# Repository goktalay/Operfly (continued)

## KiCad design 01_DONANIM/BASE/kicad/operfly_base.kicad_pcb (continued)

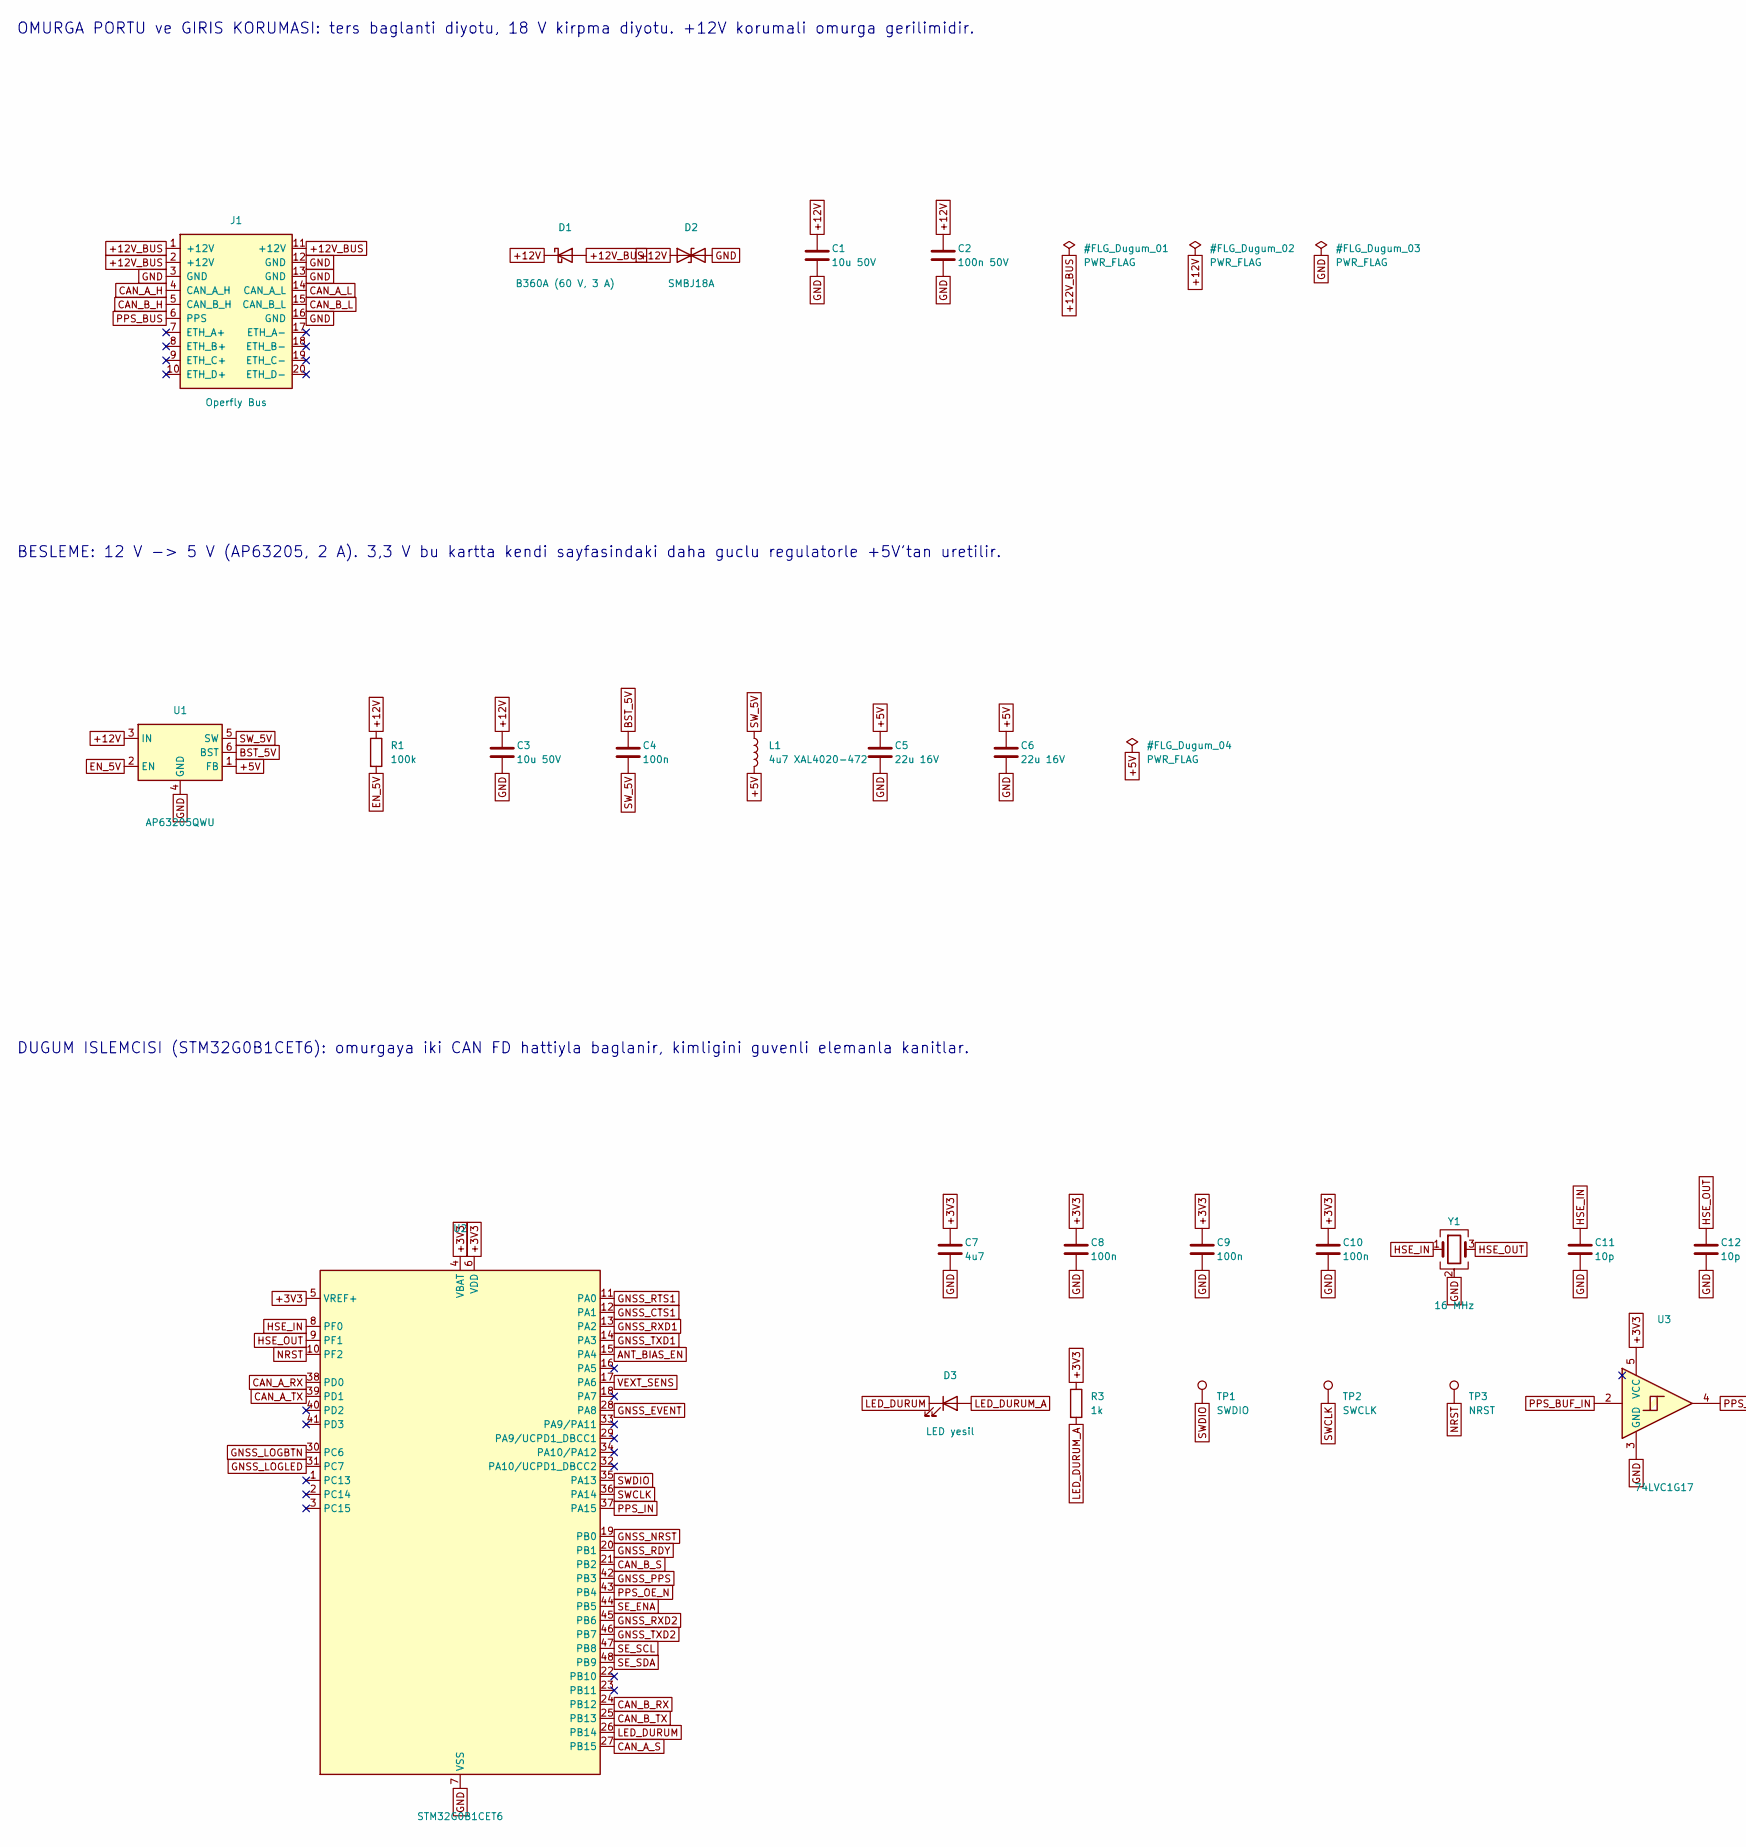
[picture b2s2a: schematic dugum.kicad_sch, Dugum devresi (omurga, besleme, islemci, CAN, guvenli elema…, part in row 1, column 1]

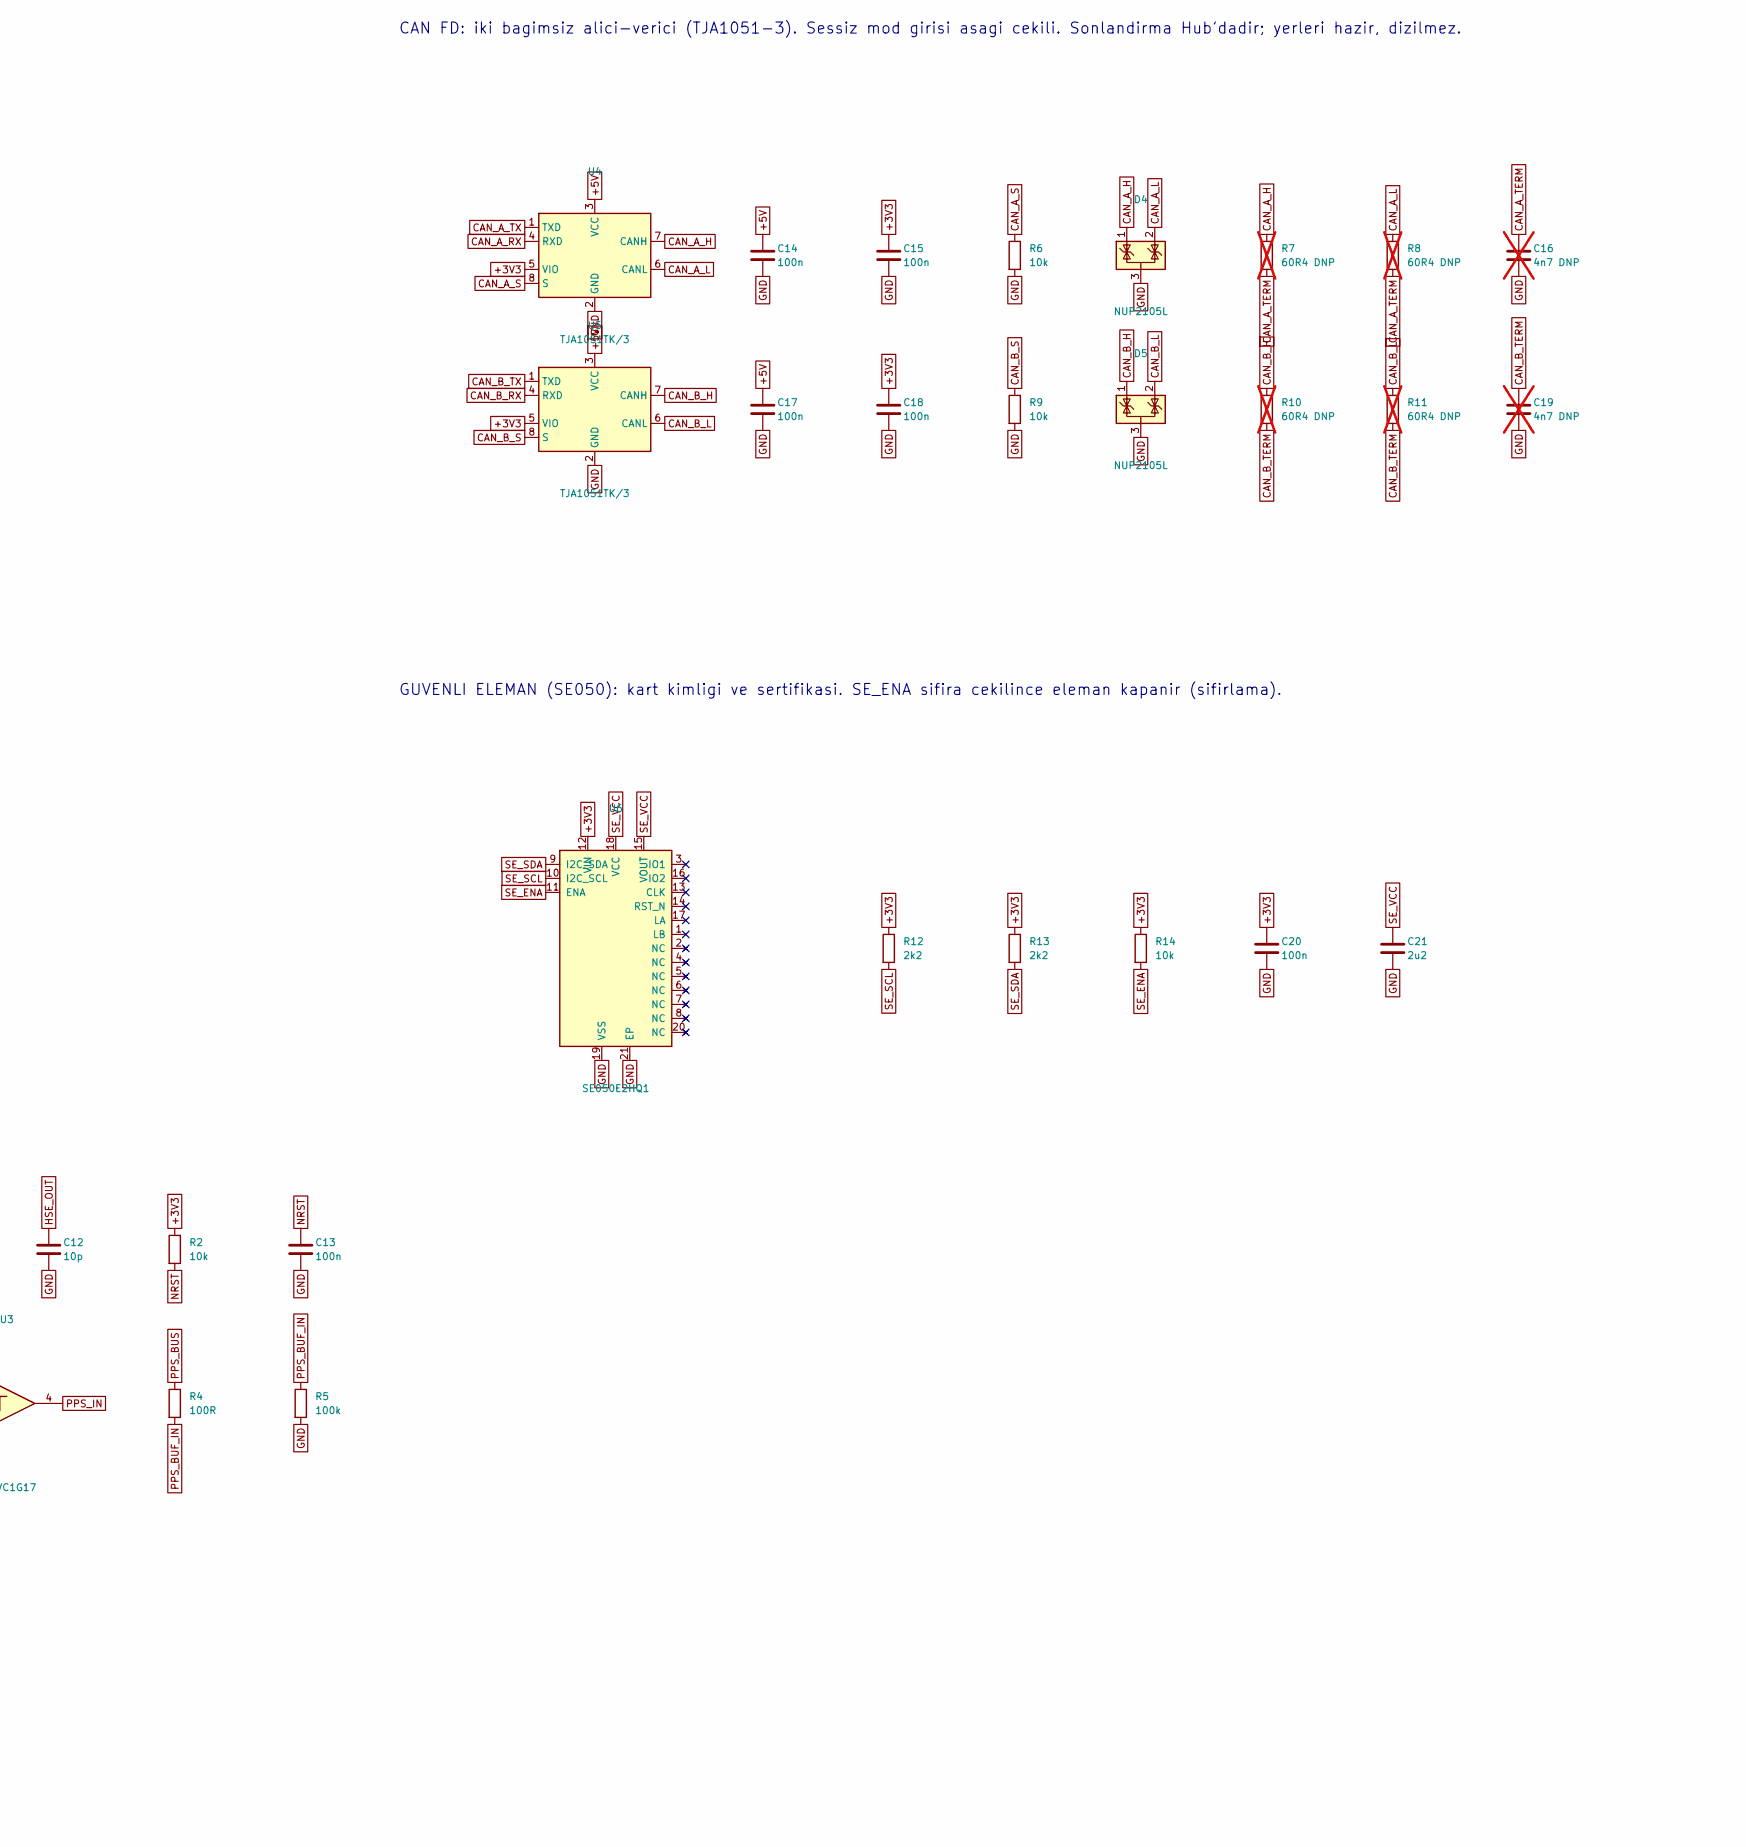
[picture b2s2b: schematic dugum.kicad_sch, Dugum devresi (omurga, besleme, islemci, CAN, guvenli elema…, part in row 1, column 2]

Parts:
C1, C3: 10u 50V; C_1206_3216Metric
C2: 100n 50V; C_0603_1608Metric
C4, C8, C9, C10, C13, C14, C15, C17, C18, C20: 100n; C_0402_1005Metric
C5, C6: 22u 16V; C_1206_3216Metric
C7: 4u7; C_0603_1608Metric
C11, C12: 10p; C_0402_1005Metric
C16, C19: 4n7 DNP; C_0402_1005Metric; not fitted
C21: 2u2; C_0603_1608Metric
D1: B360A (60 V, 3 A); D_SMA
D2: SMBJ18A; D_SMB
D3: LED yesil; LED_0603_1608Metric
D4, D5: NUP2105L; SOT-23
J1: Operfly Bus; Harwin_Gecko_G125-MS12005M2P_2x10_P1.25mm_Vertical
L1: 4u7 XAL4020-472; L_Coilcraft_XAL4020-XXX
R1, R5: 100k; R_0402_1005Metric
R2, R6, R9, R14: 10k; R_0402_1005Metric
R3: 1k; R_0402_1005Metric
R4: 100R; R_0402_1005Metric
R7, R8, R10, R11: 60R4 DNP; R_0402_1005Metric; not fitted
R12, R13: 2k2; R_0402_1005Metric
TP1: SWDIO; TestPoint_Pad_D1.0mm
TP2: SWCLK; TestPoint_Pad_D1.0mm
TP3: NRST; TestPoint_Pad_D1.0mm
U1: AP63205QWU; TSOT-23-6
U2: STM32G0B1CET6; LQFP-48_7x7mm_P0.5mm
U3: 74LVC1G17; SOT-353_SC-70-5
U4, U5: TJA1051TK/3; HVSON-8-1EP_3x3mm_P0.65mm_EP1.6x2.4mm
U6: SE050E2HQ1; QFN-20-1EP_3x3mm_P0.4mm_EP1.65x1.65mm
Y1: 16 MHz; Crystal_SMD_3225-4Pin_3.2x2.5mm

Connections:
+3V3: C7.1, C8.1, C9.1, C10.1, C15.1, C18.1, C20.1, R2.1, R3.1, R12.1, R13.1, R14.1, U2.4 (VBAT), U2.5 (VREF+), U2.6 (VDD), U3.5 (VCC), U4.5 (VIO), U5.5 (VIO), U6.12 (VIN); also elsewhere on the board
+5V: C5.1, C6.1, C14.1, C17.1, L1.2, U1.1 (FB), U4.3 (VCC), U5.3 (VCC); also elsewhere on the board
+12V: C1.1, C2.1, C3.1, D1.1 (K), D2.1 (A1), R1.1, U1.3 (IN); also elsewhere on the board
+12V_BUS: D1.2 (A), J1.1 (+12V), J1.2 (+12V), J1.11 (+12V)
ANT_BIAS_EN: U2.15 (PA4); also elsewhere on the board
BST_5V: C4.1, U1.6 (BST)
CAN_A_H: D4.1 (K), J1.4 (CAN_A_H), R7.1, U4.7 (CANH)
CAN_A_L: D4.2 (K), J1.14 (CAN_A_L), R8.1, U4.6 (CANL)
CAN_A_RX: U2.38 (PD0), U4.4 (RXD)
CAN_A_S: R6.1, U2.27 (PB15), U4.8 (S)
CAN_A_TERM: C16.1, R7.2, R8.2
CAN_A_TX: U2.39 (PD1), U4.1 (TXD)
CAN_B_H: D5.1 (K), J1.5 (CAN_B_H), R10.1, U5.7 (CANH)
CAN_B_L: D5.2 (K), J1.15 (CAN_B_L), R11.1, U5.6 (CANL)
CAN_B_RX: U2.24 (PB12), U5.4 (RXD)
CAN_B_S: R9.1, U2.21 (PB2), U5.8 (S)
CAN_B_TERM: C19.1, R10.2, R11.2
CAN_B_TX: U2.25 (PB13), U5.1 (TXD)
EN_5V: R1.2, U1.2 (EN)
GND: C1.2, C2.2, C3.2, C5.2, C6.2, C7.2, C8.2, C9.2, C10.2, C11.2, C12.2, C13.2, C14.2, C15.2, C16.2, C17.2, C18.2, C19.2, C20.2, C21.2, D2.2 (A2), D4.3 (A), D5.3 (A), J1.3 (GND), J1.12 (GND), J1.13 (GND), J1.16 (GND), R5.2, R6.2, R9.2, U1.4 (GND), U2.7 (VSS), U3.3 (GND), U4.2 (GND), U4.9 (GND), U5.2 (GND), U5.9 (GND), U6.19 (VSS), U6.21 (EP), Y1.2 (G), Y1.4 (G); also elsewhere on the board
GNSS_CTS1: U2.12 (PA1); also elsewhere on the board
GNSS_EVENT: U2.28 (PA8); also elsewhere on the board
GNSS_LOGBTN: U2.30 (PC6); also elsewhere on the board
GNSS_LOGLED: U2.31 (PC7); also elsewhere on the board
GNSS_NRST: U2.19 (PB0); also elsewhere on the board
GNSS_PPS: U2.42 (PB3); also elsewhere on the board
GNSS_RDY: U2.20 (PB1); also elsewhere on the board
GNSS_RTS1: U2.11 (PA0); also elsewhere on the board
GNSS_RXD1: U2.13 (PA2); also elsewhere on the board
GNSS_RXD2: U2.45 (PB6); also elsewhere on the board
GNSS_TXD1: U2.14 (PA3); also elsewhere on the board
GNSS_TXD2: U2.46 (PB7); also elsewhere on the board
HSE_IN: C11.1, U2.8 (PF0), Y1.1
HSE_OUT: C12.1, U2.9 (PF1), Y1.3
LED_DURUM: D3.1 (K), U2.26 (PB14)
LED_DURUM_A: D3.2 (A), R3.2
NRST: C13.1, R2.2, TP3.1, U2.10 (PF2)
PPS_BUF_IN: R4.2, R5.1, U3.2
PPS_BUS: J1.6 (PPS), R4.1; also elsewhere on the board
PPS_IN: U2.37 (PA15), U3.4
PPS_OE_N: U2.43 (PB4); also elsewhere on the board
SE_ENA: R14.2, U2.44 (PB5), U6.11 (ENA)
SE_SCL: R12.2, U2.47 (PB8), U6.10 (I2C_SCL)
SE_SDA: R13.2, U2.48 (PB9), U6.9 (I2C_SDA)
SE_VCC: C21.1, U6.15 (VOUT), U6.18 (VCC)
SWCLK: TP2.1, U2.36 (PA14)
SWDIO: TP1.1, U2.35 (PA13)
SW_5V: C4.2, L1.1, U1.5 (SW)
VEXT_SENS: U2.17 (PA6); also elsewhere on the board

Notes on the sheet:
BESLEME: 12 V -> 5 V (AP63205, 2 A). 3,3 V bu kartta kendi sayfasindaki daha guclu regulatorle +5V'tan uretilir.
GUVENLI ELEMAN (SE050): kart kimligi ve sertifikasi. SE_ENA sifira cekilince eleman kapanir (sifirlama).
DUGUM ISLEMCISI (STM32G0B1CET6): omurgaya iki CAN FD hattiyla baglanir, kimligini guvenli elemanla kanitlar.
OMURGA PORTU ve GIRIS KORUMASI: ters baglanti diyotu, 18 V kirpma diyotu. +12V korumali omurga gerilimidir.
CAN FD: iki bagimsiz alici-verici (TJA1051-3). Sessiz mod girisi asagi cekili. Sonlandirma Hub'dadir; yerleri hazir, dizilmez.

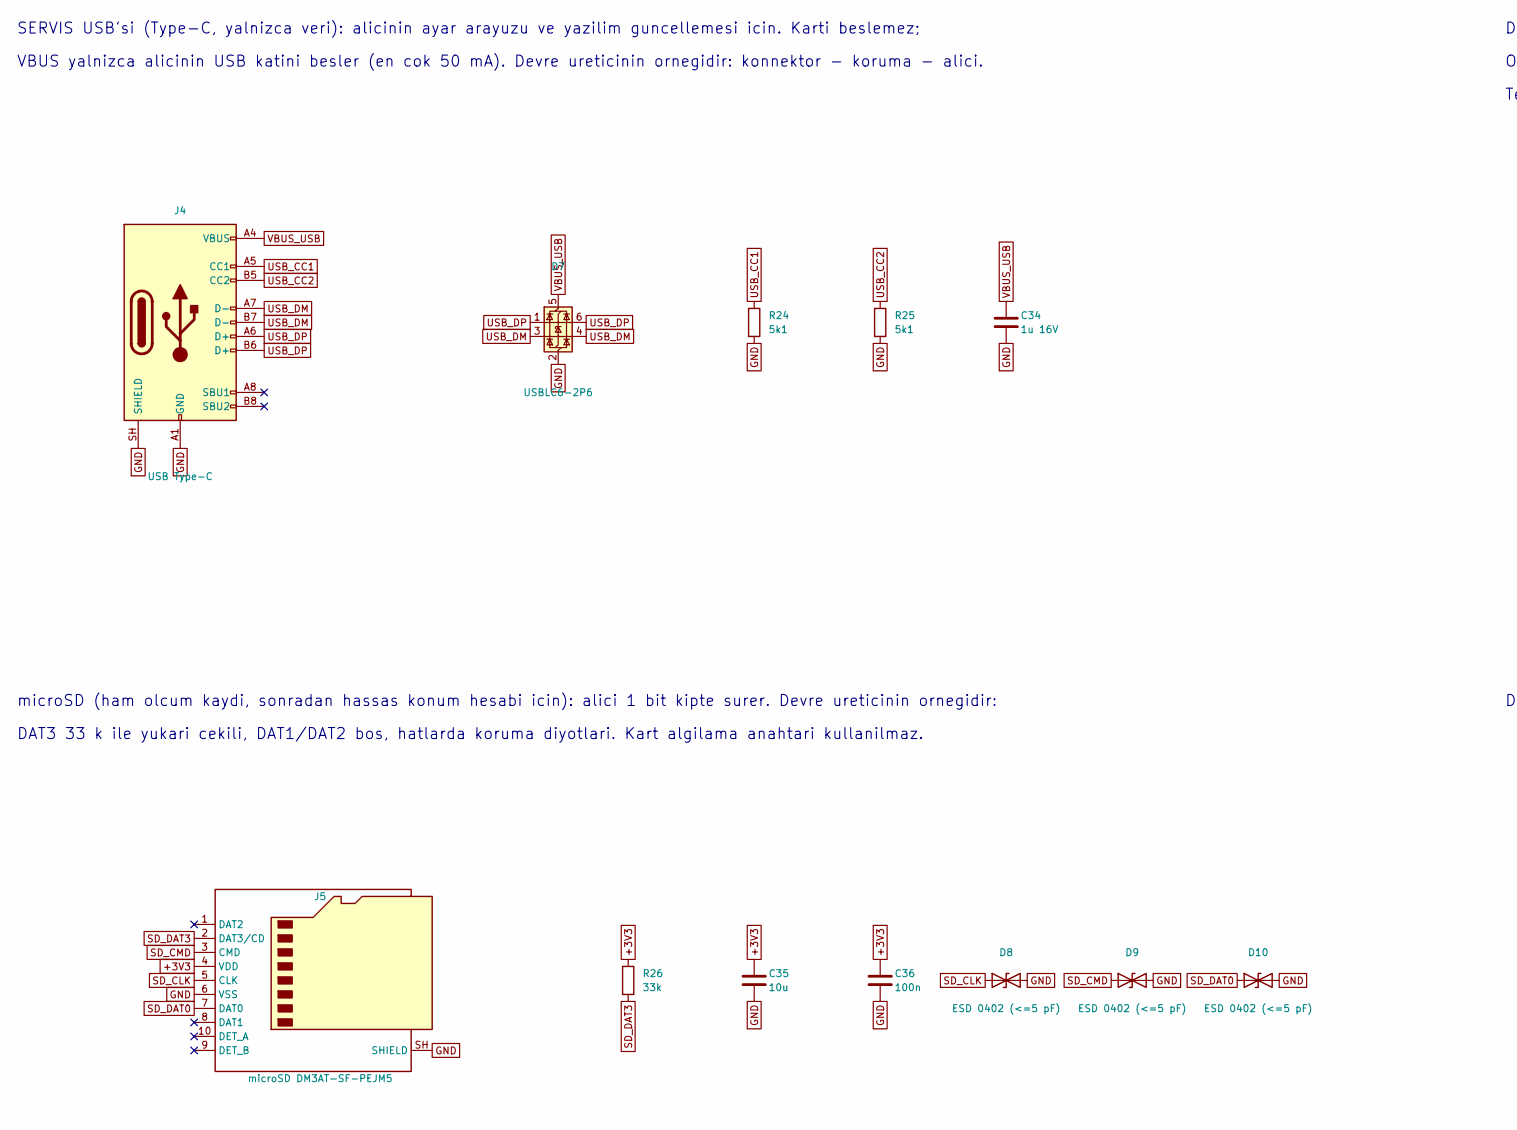
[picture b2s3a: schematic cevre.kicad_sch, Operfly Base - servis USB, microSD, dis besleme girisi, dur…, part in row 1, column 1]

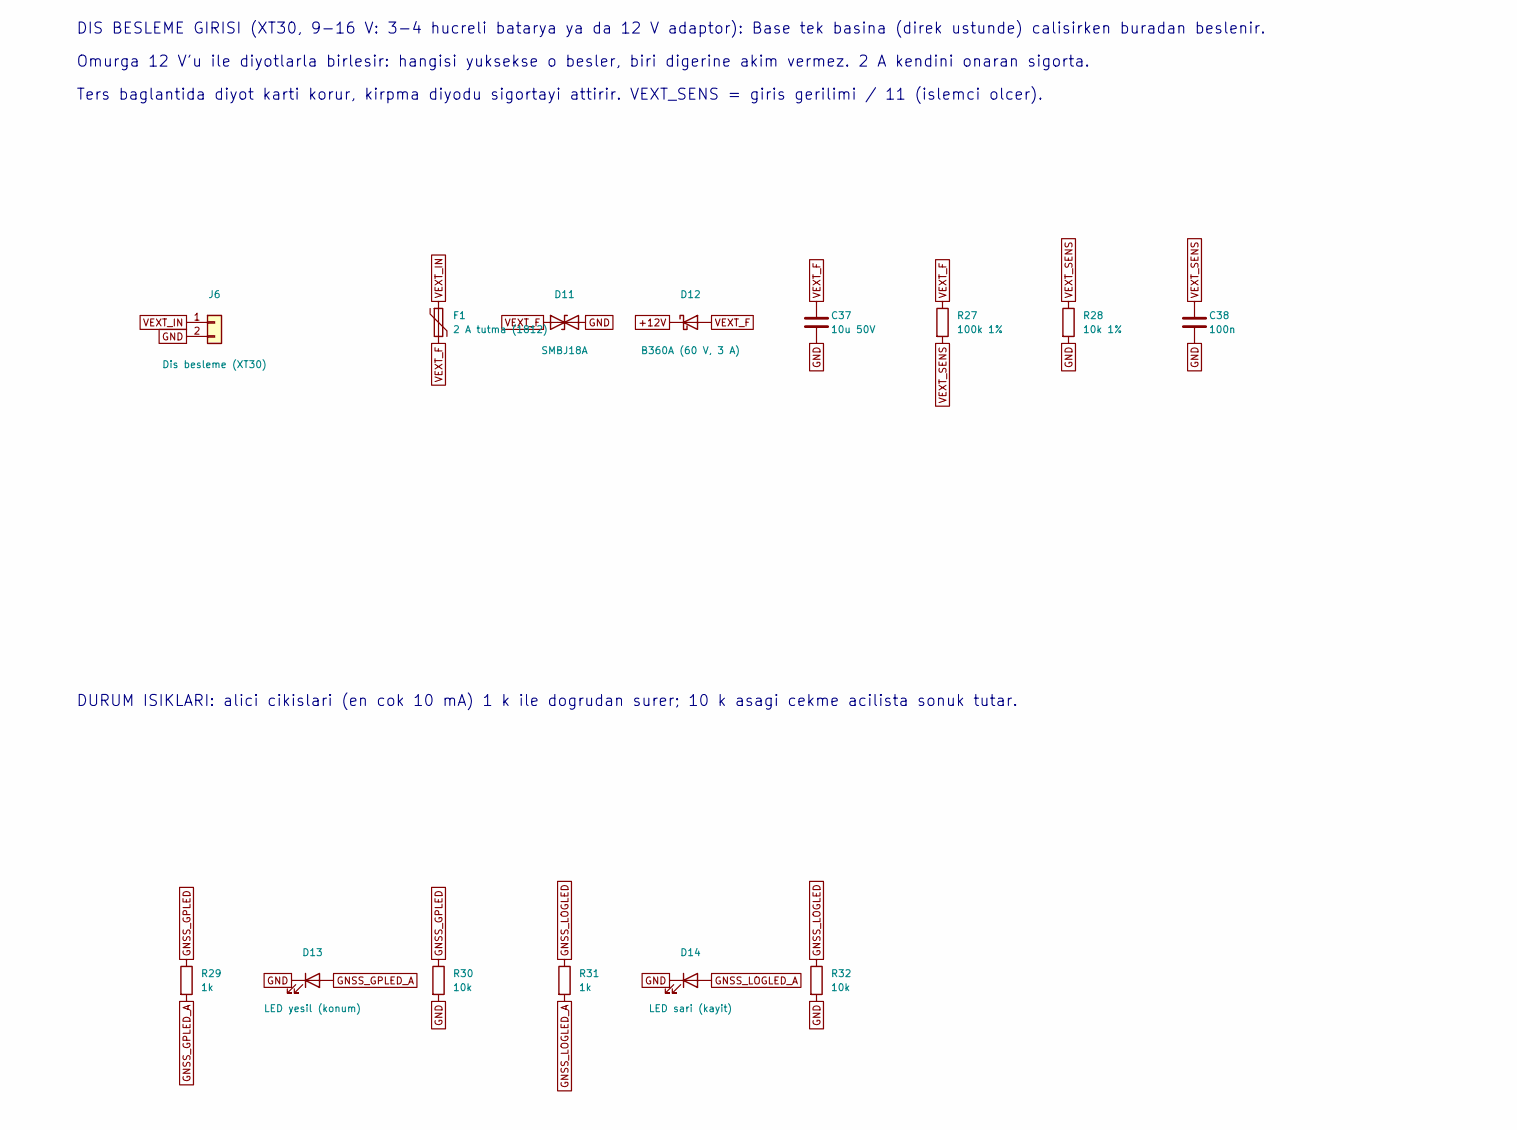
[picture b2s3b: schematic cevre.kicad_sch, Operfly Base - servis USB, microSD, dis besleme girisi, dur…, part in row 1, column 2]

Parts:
C34: 1u 16V; C_0603_1608Metric
C35: 10u; C_0805_2012Metric
C36, C38: 100n; C_0402_1005Metric
C37: 10u 50V; C_1206_3216Metric
D7: USBLC6-2P6; SOT-666
D8, D9, D10: ESD 0402 (<=5 pF); D_0402_1005Metric
D11: SMBJ18A; D_SMB
D12: B360A (60 V, 3 A); D_SMA
D13: LED yesil (konum); LED_0603_1608Metric
D14: LED sari (kayit); LED_0603_1608Metric
F1: 2 A tutma (1812); Fuse_1812_4532Metric
J4: USB Type-C; USB_C_Receptacle_GCT_USB4105-xx-A_16P_TopMnt_Horizontal
J5: microSD DM3AT-SF-PEJM5; microSD_HC_Hirose_DM3AT-SF-PEJM5
J6: Dis besleme (XT30); AMASS_XT30U-M_1x02_P5.0mm_Vertical
R24, R25: 5k1; R_0402_1005Metric
R26: 33k; R_0402_1005Metric
R27: 100k 1%; R_0402_1005Metric
R28: 10k 1%; R_0402_1005Metric
R29, R31: 1k; R_0402_1005Metric
R30, R32: 10k; R_0402_1005Metric

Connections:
+3V3: C35.1, C36.1, J5.4 (VDD), R26.1; also elsewhere on the board
+12V: D12.1 (K); also elsewhere on the board
GND: C34.2, C35.2, C36.2, C37.2, C38.2, D7.2 (GND), D8.2 (A2), D9.2 (A2), D10.2 (A2), D11.2 (A2), D13.1 (K), D14.1 (K), J4.A1 (GND), J4.A12 (GND), J4.B1 (GND), J4.B12 (GND), J4.SH (SHIELD), J5.6 (VSS), J5.SH (SHIELD), J6.2, R24.2, R25.2, R28.2, R30.2, R32.2; also elsewhere on the board
GNSS_GPLED: R29.1, R30.1; also elsewhere on the board
GNSS_GPLED_A: D13.2 (A), R29.2
GNSS_LOGLED: R31.1, R32.1; also elsewhere on the board
GNSS_LOGLED_A: D14.2 (A), R31.2
SD_CLK: D8.1 (A1), J5.5 (CLK); also elsewhere on the board
SD_CMD: D9.1 (A1), J5.3 (CMD); also elsewhere on the board
SD_DAT0: D10.1 (A1), J5.7 (DAT0); also elsewhere on the board
SD_DAT3: J5.2 (DAT3/CD), R26.2
USB_CC1: J4.A5 (CC1), R24.1
USB_CC2: J4.B5 (CC2), R25.1
USB_DM: D7.3 (I/O2), D7.4 (I/O2), J4.A7 (D-), J4.B7 (D-); also elsewhere on the board
USB_DP: D7.1 (I/O1), D7.6 (I/O1), J4.A6 (D+), J4.B6 (D+); also elsewhere on the board
VBUS_USB: C34.1, D7.5 (VBUS), J4.A4 (VBUS), J4.A9 (VBUS), J4.B4 (VBUS), J4.B9 (VBUS); also elsewhere on the board
VEXT_F: C37.1, D11.1 (A1), D12.2 (A), F1.2, R27.1
VEXT_IN: F1.1, J6.1
VEXT_SENS: C38.1, R27.2, R28.1; also elsewhere on the board

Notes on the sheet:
microSD (ham olcum kaydi, sonradan hassas konum hesabi icin): alici 1 bit kipte surer. Devre ureticinin ornegidir:
DIS BESLEME GIRISI (XT30, 9-16 V: 3-4 hucreli batarya ya da 12 V adaptor): Base tek basina (direk ustunde) calisirken buradan beslenir.
SERVIS USB'si (Type-C, yalnizca veri): alicinin ayar arayuzu ve yazilim guncellemesi icin. Karti beslemez;
VBUS yalnizca alicinin USB katini besler (en cok 50 mA). Devre ureticinin ornegidir: konnektor - koruma - alici.
DURUM ISIKLARI: alici cikislari (en cok 10 mA) 1 k ile dogrudan surer; 10 k asagi cekme acilista sonuk tutar.
Omurga 12 V'u ile diyotlarla birlesir: hangisi yuksekse o besler, biri digerine akim vermez. 2 A kendini onaran sigorta.
Ters baglantida diyot karti korur, kirpma diyodu sigortayi attirir. VEXT_SENS = giris gerilimi / 11 (islemci olcer).
DAT3 33 k ile yukari cekili, DAT1/DAT2 bos, hatlarda koruma diyotlari. Kart algilama anahtari kullanilmaz.
